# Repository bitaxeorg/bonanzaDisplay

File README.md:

# bonanzaDisplay v3.1

bonanzaDisplay is an open hardware OLED display and rotary-encoder controller
for **bitaxeBonanza-1004x**. An onboard Raspberry Pi RP2354A drives the display,
reads the encoder and its push button, and connects to the host ESP32 through
a single flat-flex cable carrying power, communication signals, and debug access.

This repository contains the **v3.1 KiCad hardware design**. Firmware, the
display UI, and the host communication protocol are not included here.

*Component-side render; the OLED panel faces the other side of the board.*

## Hardware overview

| Function | Implementation |
| --- | --- |
| Controller | Raspberry Pi RP2354A |
| Display | 3.12-inch, 256 × 64 OLED module using an SSD1322 controller |
| Display interface | 8-bit 8080 parallel bus |
| User input | Rotary encoder with push button (SW3) |
| Host connection | 12-pin, 1.0 mm pitch FFC connector (J5) |
| Host signals | TX/RX, two GPIO signals, SWDIO, and SWCLK |
| Power input | Nominal 12 V through J5 or the J2 bench-power pads |
| Logic supply | 3.3 V from a TPS62933 buck regulator |
| Development | USB-C (J6), SWD pads (J15), BOOT and RESET buttons |
| PCB | Six layers, with filled and copper-capped through vias |

The RP2354A handles the display and local controls, allowing the host to send
application data rather than drive the OLED bus directly. The actual UI and
division of work between the two processors depend on firmware.

## Connecting the board

### Host cable and J5 pinout

The intended connection is display J5 to **J5 on bitaxeBonanza-1004x**:

- Display connector: **JUSHUO AFA01-S12FCA-00**, LCSC C262757, bottom contact.
- Host connector: **TE 1-1735042-2**, LCSC C3169702.
- Cable: **12 conductors, 1.0 mm pitch, same-side exposed contacts**, with
  nominal 0.3 mm mating thickness. An example is SHOUHAN FFC-1.0-12P-50mm,
  **LCSC C6936374**.

For this connector pair, the standard same-side cable connects display pin
`n` to host pin `13 − n`. This numbering reversal is intentional; a custom
crossover cable is not required. Verify pin 1 and contact orientation before
applying power, since an incorrect connection can put 12 V on debug signals.

| Display J5 pin | Host J5 pin | Display net | RP2354A connection |
| --- | --- | --- | --- |
| 1 | 12 | 12V | Power input |
| 2 | 11 | 12V | Power input |
| 3 | 10 | GND | Ground |
| 4 | 9 | GND | Ground |
| 5 | 8 | DISP_GPIO1 | GPIO22 |
| 6 | 7 | DISP_GPIO2 | GPIO23 |
| 7 | 6 | GND | Ground |
| 8 | 5 | DISP_TX | GPIO21 |
| 9 | 4 | DISP_RX | GPIO20 |
| 10 | 3 | GND | Ground |
| 11 | 2 | SWD | SWDIO |
| 12 | 1 | SWCLK | SWCLK |

TX/RX above are the schematic net names. Firmware must implement the serial
interface on these exact GPIOs; the names do not establish a hardware UART
pin-mux configuration.

At the display's bottom-contact connector, the exposed cable contacts face
the PCB. At the TE host connector, they face the even-numbered solder-tail
side. Connector verification is recorded in
[issue #16](https://github.com/bitaxeorg/bonanzaDisplay/issues/16).

### OLED module and J1

J1 is a **JUSHUO AFC07-S30ECA-00** (LCSC C262645), a 30-contact, 0.5 mm pitch,
top-contact connector for nominal 0.3 mm flex. The OLED ribbon's physical
fit and contact orientation have been checked against the intended module.

The [EA W256064-XALG datasheet](https://www.lcd-module.de/fileadmin/html-seiten/eng/pdf/grafik/W256064-XALG.pdf)
is the reference for the module interface and electrical requirements.
Similar modules are sold under several manufacturer part numbers; check the
pinout, voltage requirements, and ribbon orientation of the exact module
being purchased rather than relying on screen size or controller name alone.

**Keep the project's custom J1 footprint.** Its pad numbers follow the OLED
module's numbering: KiCad pad `n` corresponds to connector drawing circuit
`31 − n`. Replacing it with a generic footprint without checking this mapping
can reverse the interface. Pads 31 and 32 are the grounded mounting tabs.

### Power

The host normally supplies 12 V through J5. For standalone development,
supply **J2 pin 1 with 12 V and J2 pin 2 with GND**. J2 is an optional header
location; the header is excluded from the current PCBA assembly selection.
**USB does not power the board.**

U4 converts 12 V to 3.3 V for the MCU and OLED logic. The OLED's VCI and
VDDIO inputs both use 3.3 V; separate 3.0 V and 2.8 V regulators are not
needed in this revision. The RP2354A's internal regulator supplies its core
through L1.

The OLED panel supply, VCC, connects directly to 12 V. There is no MCU-controlled
load switch or independent VCC sequencing. This is an accepted limitation of
v3.1, tracked in [issue #7](https://github.com/bitaxeorg/bonanzaDisplay/issues/7).
Firmware delays cannot switch this hardwired rail.

## Firmware interfaces

### Display

The hardware straps select **8-bit 8080 mode** (BS1 high, BS0 low).

| Function | RP2354A GPIO | J1 pin |
| --- | --- | --- |
| D0–D7 | GPIO0–GPIO7, respectively | 13 down to 6 |
| Reset, active low | GPIO8 | 20 |
| Chip select, active low | GPIO9 | 19 |
| Data/command | GPIO10 | 18 |
| Write strobe, active low | GPIO11 | 15 |
| Read strobe, active low | GPIO12 | 14 |

Use 8080 bus timing, and keep RD inactive for write-only operation. The
reference module's example SPI transport cannot be copied unchanged.

The OLED's VDD pin has a bypass capacitor but no external supply, so
initialization must enable the SSD1322's internal VDD regulator. Initialization
must also match the fitted external VSL diode/resistor network and the exact
module's reset and startup timing. See the reference module datasheet above.

### Encoder

| SW3 contact / net | RP2354A GPIO | Pull-up to 3.3 V |
| --- | --- | --- |
| B / SW_CW | GPIO13 | R41, 4.7 kΩ |
| S / SW_SW (push button) | GPIO14 | R42, 4.7 kΩ |
| A / SW_CCW | GPIO15 | R43, 4.7 kΩ |

The common contact is grounded. External 4.7 kΩ pull-ups provide approximately
0.70 mA through each closed contact, exceeding the selected HanElectricity
encoder's 0.5 mA minimum per phase. The MCU's internal pull-ups alone do not
meet that contact-current specification. R41–R43 use UNI-ROYAL
0402WGF4701TCE / LCSC C25900, a 0402, ±1% resistor listed as a JLCPCB Basic part
when selected. See the [encoder datasheet, page 2](https://datasheet.lcsc.com/datasheet/pdf/48f6c88fa6dacc08326345335965b3eb.pdf).

Configure the GPIOs as inputs with internal pull-downs disabled; external
resistors provide the pull-ups. Implement quadrature decoding and switch
debounce, and confirm rotation direction on the assembled board. The CW/CCW
net labels alone do not determine the decoder's sign.

## Programming and development

SW1 is **RESET** and SW2 is **BOOT**. The BOOT button connects to the QSPI
chip-select signal through R40, a 1 kΩ series resistor.

For SWD, use the host connector or the optional J15 header pads:

| J15 pin | Signal |
| --- | --- |
| 1 | SWCLK |
| 2 | GND |
| 3 | SWDIO |

Use a debugger compatible with 3.3 V logic and power the board externally.
J15 does not provide a target-voltage reference pin, and its header is excluded
from the current PCBA assembly selection.

The intended field-update path is the host ESP32 programming the RP2354A
through J5's SWD signals. ESP32 SWD support and the complete field-update
workflow still require firmware implementation and validation.

### Development-only USB port

J6 provides USB for development with external 12 V power. This revision
intentionally accepts the following limitations:

- **No VBUS sensing.** VBUS connects only to J6 and test point TP64. The MCU
  cannot detect when a host or hub removes VBUS, so its D+ attachment pull-up
  can remain enabled while the board stays powered. This does not meet the
  USB requirement to remove the attachment pull-up when VBUS is absent and
  can source current into an unpowered host's data input. Disconnect USB
  before shutting down the host/hub or disabling its port power while the
  board remains on. Normal suspend with VBUS present is a different condition.
- **No external USB ESD array.** The port relies on the MCU's internal
  protection and has not been validated for exposed production use or
  system-level ESD immunity. Use normal ESD precautions during development.

These choices are recorded in
[issue #14](https://github.com/bitaxeorg/bonanzaDisplay/issues/14); they are not
a claim of full USB compliance. Revisit them if USB becomes a user-facing port.

A future production variant could omit J6 and USB-only resistors R2, R4,
R37, and R38. **The current design still fits these parts**; no USB DNP
assembly variant has been implemented.

## Working with the design

Open [bonanzaDisplay.kicad_pro](bonanzaDisplay.kicad_pro) in **KiCad 10**.
Keep the repository's library tables, custom libraries, and 3D models together;
the library tables use project-relative paths.

| Path | Contents |
| --- | --- |
| [bonanzaDisplay.kicad_sch](bonanzaDisplay.kicad_sch) | Schematic |
| [bonanzaDisplay.kicad_pcb](bonanzaDisplay.kicad_pcb) | Six-layer PCB layout |
| [bonanzaDisplay.kicad_dru](bonanzaDisplay.kicad_dru) | Custom fabrication rules |
| [bonanzaDisplay.kicad_sym](bonanzaDisplay.kicad_sym) | Project symbol library |
| [bonanzaDisplay.pretty/](bonanzaDisplay.pretty/) | Project footprints |
| [3dshapes/](3dshapes/) | Component and module models |
| [fabrication-toolkit-options.json](fabrication-toolkit-options.json) | Saved Fabrication Toolkit export options |
| [docs/manufacturing.md](docs/manufacturing.md) | Fabrication, via filling, stencil, and assembly requirements |

After schematic changes, update the PCB, refill zones, and run ERC and DRC
including schematic/PCB parity before generating new manufacturing outputs.
Preserve the intentional connector numbering and review placement offsets
when replacing footprints or changing export tools.

## Manufacturing and project status

The board targets JLCPCB's standard **six-layer, 1 oz outer-copper process
with a routed outline**. It requires **epoxy-filled and copper-capped vias
(POFV)**, including vias in solder pads. Tenting alone is insufficient.
The design was reviewed against JLCPCB's no-extra-cost six-layer options on
2026-10-14; confirm the actual quote and process selections when ordering.

Read the [manufacturing guide](docs/manufacturing.md) before generating or
uploading Gerbers, a BOM, or a component placement file. The OLED module and
host FFC cable are separate assembly items, not parts installed by the board
assembly BOM.

At hardware commit [`0fab1ca`](https://github.com/bitaxeorg/bonanzaDisplay/commit/0fab1cac237adbfad9c7c31abaaa868e837f4df0),
KiCad 10.0.6 checks passed with no ERC findings, DRC violations, unconnected
items, or schematic/PCB parity findings. These checks do not establish
assembled-board operation or approve a production order. Remaining work includes:

- Resolving the effective-capacitance and inductor qualification findings in
  the [selected-part ratings review](docs/part-ratings.md).
- Checking final supplier part matches and placement corrections after the
  source BOM metadata reconciliation
  ([#13](https://github.com/bitaxeorg/bonanzaDisplay/issues/13)).
- Confirming filled/capped vias and the supplier's final stencil/CAM treatment
  ([#12](https://github.com/bitaxeorg/bonanzaDisplay/issues/12)).
- Reviewing the final assembly preview and validating firmware and assembled
  hardware, including display startup, encoder input, oscillator operation,
  BOOT, USB, and the intended host update workflow
  ([#17](https://github.com/bitaxeorg/bonanzaDisplay/issues/17)).

Use the [issue tracker](https://github.com/bitaxeorg/bonanzaDisplay/issues)
for review findings, accepted limitations, and their resolution. When reporting
a problem, include the board revision, hardware/firmware commits, exact OLED
module, and steps to reproduce it.

## License

The hardware design is licensed under the
**CERN Open Hardware Licence v2 — Strongly Reciprocal (CERN-OHL-S-2.0)**.
See [LICENSE](LICENSE) for the full terms.

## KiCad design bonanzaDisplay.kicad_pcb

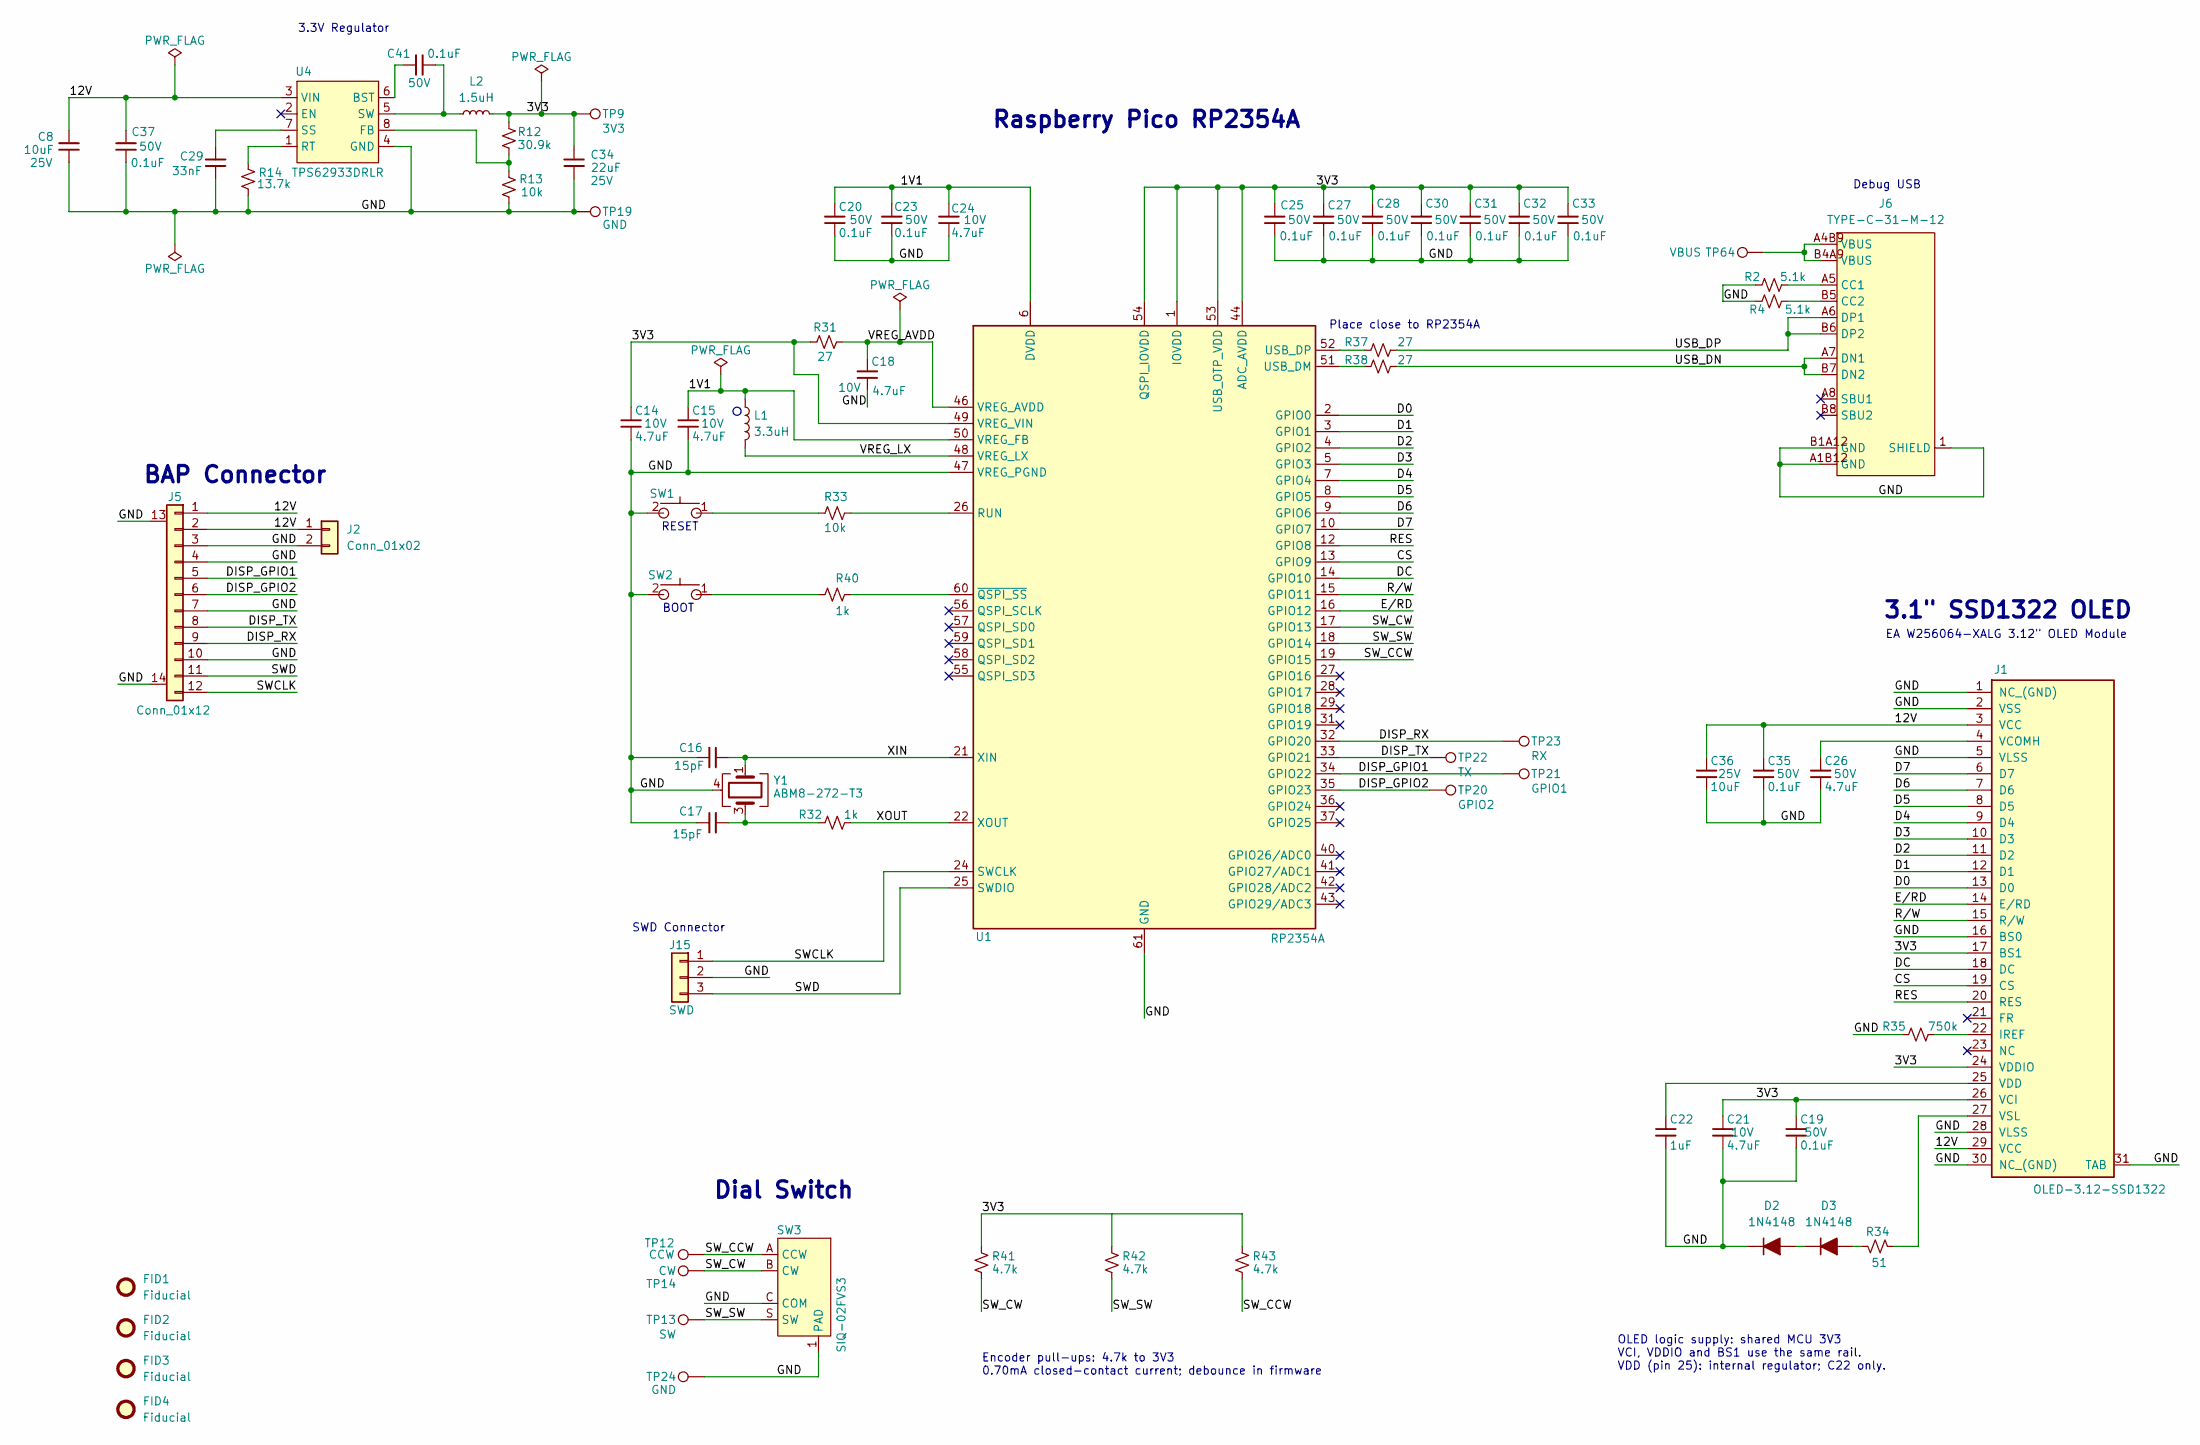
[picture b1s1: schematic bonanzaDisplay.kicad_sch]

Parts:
C8: 10uF; C_0805_2012Metric; Voltage 25V; Tolerance ±10%; PARTNO CL21A106KAYNNNE; LCSC C15850
C14: 4.7uF; C_0402_1005Metric; Voltage 10V; Previous voltage requir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 6.6V; PARTNO CL05A475MP5NRNC; LCSC C23733
C15, C18, C24: 4.7uF; C_0402_1005Metric; Voltage 10V; Previous voltage requir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 2.2V; PARTNO CL05A475MP5NRNC; LCSC C23733
C16, C17: 15pF; C_0402_1005Metric; Tolerance ±5%; Voltage 50V; PARTNO 0402CG150J500NT; LCSC C1548
C19: 0.1uF; C_0402_1005Metric; Voltage 50V; Previous voltage requir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 6V; PARTNO GRM155R71H104KE14D; LCSC C77020
C20, C23: 0.1uF; C_0402_1005Metric; Voltage 50V; Previous voltage requir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 2.2V; PARTNO GRM155R71H104KE14D; LCSC C77020
C21: 4.7uF; C_0402_1005Metric; Voltage 10V; Previous voltage requir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 6V; PARTNO CL05A475MP5NRNC; LCSC C23733
C22: 1uF; C_0402_1005Metric; Tolerance ±10%; Voltage 25V; PARTNO CL05A105KA5NQNC; LCSC C52923
C25, C27, C28, C30, C31, C32, C33: 0.1uF; C_0402_1005Metric; Voltage 50V; Previous voltage requir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 6.6V; PARTNO GRM155R71H104KE14D; LCSC C77020
C26: 4.7uF; C_1206_3216Metric; Tolerance ±10%; Voltage 50V; PARTNO CL31B475KBHNNNE; LCSC C51205
C29: 33nF; C_0402_1005Metric; Tolerance ±10%; Voltage 50V; PARTNO CC0402KRX7R9BB333; LCSC C106862
C34: 22uF; C_0805_2012Metric; Voltage 25V; Previous voltage requir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 10V; PARTNO CL21A226MAQNNNE; LCSC C45783
C35: 0.1uF; C_0402_1005Metric; Voltage 50V; Previous voltage requir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 24V; PARTNO GRM155R71H104KE14D; LCSC C77020
C36: 10uF; C_0805_2012Metric; Voltage 25V; Previous voltage requir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 24V; PARTNO CL21A106KAYNNNE; LCSC C15850
C37: 0.1uF; C_0402_1005Metric; Voltage 50V; Previous voltage requir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 25V; PARTNO GRM155R71H104KE14D; LCSC C77020
C41: 0.1uF; C_0402_1005Metric; Voltage 50V; Previous voltage requir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 10V; PARTNO GRM155R71H104KE14D; LCSC C77020
D2, D3: 1N4148; D_SOD-523; PARTNO 1N4148WT; LCSC C917006
FID1, FID2, FID3, FID4: Fiducial; Fiducial_1mm_Mask2mm
J1: OLED-3.12-SSD1322; FPC-SMD_P0.50-30P_LCS-SJ-H2.0; PARTNO AFC07-S30ECA-00; LCSC C262645
J2: Conn_01x02; PinHeader_1x02_P2.54mm_Vertical
J5: Conn_01x12; FPC-SMD_12P-P1.00_FGS-XJ-H2.0; PARTNO AFA01-S12FCA-00; LCSC C262757
J6: TYPE-C-31-M-12; USB-C_SMD-TYPE-C-31-M-12_1; PARTNO TYPE-C-31-M-12; LCSC C165948
J15: SWD; PinHeader_1x03_P2.54mm_Vertical
L1: 3.3uH; IND-SMD-L2.0-W1.6-MLP2016H3R3MT0S1; PARTNO MLP2016H3R3MT0S1; LCSC C383379
L2: 1.5uH; IND-SMD_L2.0-W1.6; PARTNO FTC201612S1R5MBCA; LCSC C5832350
R2, R4: 5.1k; R_0402_1005Metric; Tolerance ±1%; Voltage 50V; PARTNO 0402WGF5101TCE; LCSC C25905
R12: 30.9k; R_0402_1005Metric; Tolerance ±1%; Voltage 50V; PARTNO 0402WGF3092TCE; LCSC C270615
R13, R33: 10k; R_0402_1005Metric; Tolerance ±1%; Voltage 50V; PARTNO 0402WGF1002TCE; LCSC C25744
R14: 13.7k; R_0402_1005Metric; Tolerance ±1%; Voltage 50V; PARTNO RC0402FR-0713K7L; LCSC C274888
R31, R37, R38: 27; R_0402_1005Metric; Tolerance ±1%; Voltage 50V; PARTNO RC0402FR-0727RL; LCSC C138021
R32: 1k; R_0402_1005Metric; Tolerance ±1%; Voltage 50V; PARTNO 0402WGF1001TCE; LCSC C11702
R34: 51; R_0402_1005Metric; Tolerance ±1%; Voltage 50V; PARTNO RC0402FR-0751RL; LCSC C137960
R35: 750k; R_0402_1005Metric; Tolerance ±1%; Voltage 50V; PARTNO 0402WGF7503TCE; LCSC C122545
R40: 1k; R_0402_1005Metric; Tolerance ±1%; Voltage 50V; MPN 0402WGF1001TCE; LCSC C11702
R41, R42, R43: 4.7k; R_0402_1005Metric; Tolerance ±1%; Voltage 50V; PARTNO 0402WGF4701TCE; LCSC C25900
SW1, SW2: TS-1088-AR02016; SW-SMD_L3.9-W3.0-P4.45; PARTNO TS-1088-AR02016; LCSC C720477
SW3: SIQ-02FVS3; SW-SMD_SIQ-02FVS3; PARTNO SIQ-02FVS3; LCSC C41430892
TP9: 3V3; TestPoint_Pad_D1.0mm
TP12: CCW; TestPoint_Pad_D1.0mm
TP13: SW; TestPoint_Pad_D1.0mm
TP14: CW; TestPoint_Pad_D1.0mm; LCSC C344022
TP19, TP24: GND; TestPoint_Pad_D1.0mm; LCSC C138021
TP20: GPIO2; TestPoint_Pad_D1.0mm
TP21: GPIO1; TestPoint_Pad_D1.0mm
TP22: TX; TestPoint_Pad_D1.0mm
TP23: RX; TestPoint_Pad_D1.0mm
TP64: VBUS; TestPoint_Pad_D1.0mm
U1: RP2354A; QFN-60-1EP_7x7mm_P0.4mm_EP3.4x3.4mm; PARTNO RP2354A; LCSC C41378174
U4: TPS62933DRLR; SOT-583-8_L2.1-W1.2-P0.50-LS1.6-BR; PARTNO TPS62933DRLR; LCSC C3200405
Y1: ABM8-272-T3; Crystal_SMD_3225-4Pin_3.2x2.5mm; PARTNO ABM8-272-T3; LCSC C20625731

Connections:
/1V1: C15.1, C20.1, C23.1, C24.1, L1.1, U1.6 (DVDD), U1.23 (DVDD), U1.39 (DVDD), U1.50 (VREG_FB)
/3V3: C14.1, C19.1, C21.1, C25.1, C27.1, C28.1, C30.1, C31.1, C32.1, C33.1, C34.2, J1.17 (BS1), J1.24 (VDDIO), J1.26 (VCI), L2.2, R12.2, R31.2, R41.1, R42.1, R43.1, TP9.1 (1_1), U1.1 (IOVDD), U1.11 (IOVDD), U1.20 (IOVDD), U1.30 (IOVDD), U1.38 (IOVDD), U1.44 (ADC_AVDD), U1.45 (IOVDD), U1.49 (VREG_VIN), U1.53 (USB_OTP_VDD), U1.54 (QSPI_IOVDD)
/12V: C8.2, C35.1, C36.1, C37.1, J1.3 (VCC), J1.29 (VCC), J2.1, J5.1, J5.2, U4.3 (VIN)
/CS: J1.19 (CS), U1.13 (GPIO9)
/D0: J1.13 (D0), U1.2 (GPIO0)
/D1: J1.12 (D1), U1.3 (GPIO1)
/D2: J1.11 (D2), U1.4 (GPIO2)
/D3: J1.10 (D3), U1.5 (GPIO3)
/D4: J1.9 (D4), U1.7 (GPIO4)
/D5: J1.8 (D5), U1.8 (GPIO5)
/D6: J1.7 (D6), U1.9 (GPIO6)
/D7: J1.6 (D7), U1.10 (GPIO7)
/DC: J1.18 (DC), U1.14 (GPIO10)
/DISP_GPIO1: J5.5, TP21.1 (1_1), U1.34 (GPIO22)
/DISP_GPIO2: J5.6, TP20.1 (1_1), U1.35 (GPIO23)
/DISP_RX: J5.9, TP23.1 (1_1), U1.32 (GPIO20)
/DISP_TX: J5.8, TP22.1 (1_1), U1.33 (GPIO21)
/E/RD: J1.14 (E/RD), U1.16 (GPIO12)
/GND: C8.1, C14.2, C15.2, C16.2, C17.2, C18.2, C19.2, C20.2, C21.2, C22.2, C23.2, C24.2, C25.2, C26.2, C27.2, C28.2, C29.1, C30.2, C31.2, C32.2, C33.2, C34.1, C35.2, C36.2, C37.2, D2.1 (K), J1.1 (NC_(GND)), J1.2 (VSS), J1.5 (VLSS), J1.16 (BS0), J1.28 (VLSS), J1.30 (NC_(GND)), J1.31 (TAB), J1.32 (TAB), J2.2, J5.3, J5.4, J5.7, J5.10, J5.13, J5.14, J6.1 (SHIELD), J6.2 (EH), J6.3 (EH), J6.4 (EH), J6.A1B12 (GND), J6.B1A12 (GND), J15.2, R2.1, R4.1, R13.1, R14.1, R35.2, SW1.2, SW2.2, SW3.1 (PAD), SW3.2 (PAD), SW3.C (COM), TP19.1 (1_1), TP24.1 (1_1), U1.47 (VREG_PGND), U1.61 (GND), U4.4 (GND), Y1.2, Y1.4
/RES: J1.20 (RES), U1.12 (GPIO8)
/R/W: J1.15 (R/W), U1.15 (GPIO11)
/SWCLK: J5.12 (Pin_10), J15.1, U1.24 (SWCLK)
/SWD: J5.11 (Pin_10), J15.3, U1.25 (SWDIO)
/SW_CCW: R43.2, SW3.A (CCW), TP12.1 (1_1), U1.19 (GPIO15)
/SW_CW: R41.2, SW3.B (CW), TP14.1 (1_1), U1.17 (GPIO13)
/SW_SW: R42.2, SW3.S (SW), TP13.1 (1_1), U1.18 (GPIO14)
/USB_DN: J6.A7 (DN1), J6.B7 (DN2), R38.1
/USB_DP: J6.A6 (DP1), J6.B6 (DP2), R37.1
/VREG_AVDD: C18.1, R31.1, U1.46 (VREG_AVDD)
/VREG_LX: L1.2, U1.48 (VREG_LX)
/XIN: C16.1, U1.21 (XIN), Y1.1
/XOUT: R32.1, U1.22 (XOUT)
unnamed: C17.1, R32.2, Y1.3
unnamed: D2.2 (A), D3.1 (K)
unnamed: D3.2 (A), R34.1
unnamed: J1.22 (IREF), R35.1
unnamed: C26.1, J1.4 (VCOMH)
unnamed: C22.1, J1.25 (VDD)
unnamed: J1.27 (VSL), R34.2
unnamed: J6.A5 (CC1), R2.2
unnamed: J6.B5 (CC2), R4.2
unnamed: J6.A4B9 (VBUS), J6.B4A9 (VBUS), TP64.1 (1_1)
unnamed: R33.2, SW1.1
unnamed: R40.2, SW2.1
unnamed: R33.1, U1.26 (RUN)
unnamed: R38.2, U1.51 (USB_DM)
unnamed: R37.2, U1.52 (USB_DP)
unnamed: R40.1, U1.60 (~QSPI_SS)
unnamed: C41.1, U4.6 (BST)
unnamed: R12.1, R13.2, U4.8 (FB)
unnamed: R14.2, U4.1 (RT)
unnamed: C29.2, U4.7 (SS)
unnamed: C41.2, L2.1, U4.5 (SW)

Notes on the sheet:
Place close to RP2354A
Encoder pull-ups: 4.7k to 3V3 0.70mA closed-contact current; debounce in firmware
EA W256064-XALG 3.12" OLED Module
Debug USB
BOOT
SWD Connector
Raspberry Pico RP2354A
3.3V Regulator
OLED logic supply: shared MCU 3V3 VCI, VDDIO and BS1 use the same rail. VDD (pin 25): internal regulator; C22 only.
Dial Switch
3.1" SSD1322 OLED
BAP Connector
RESET

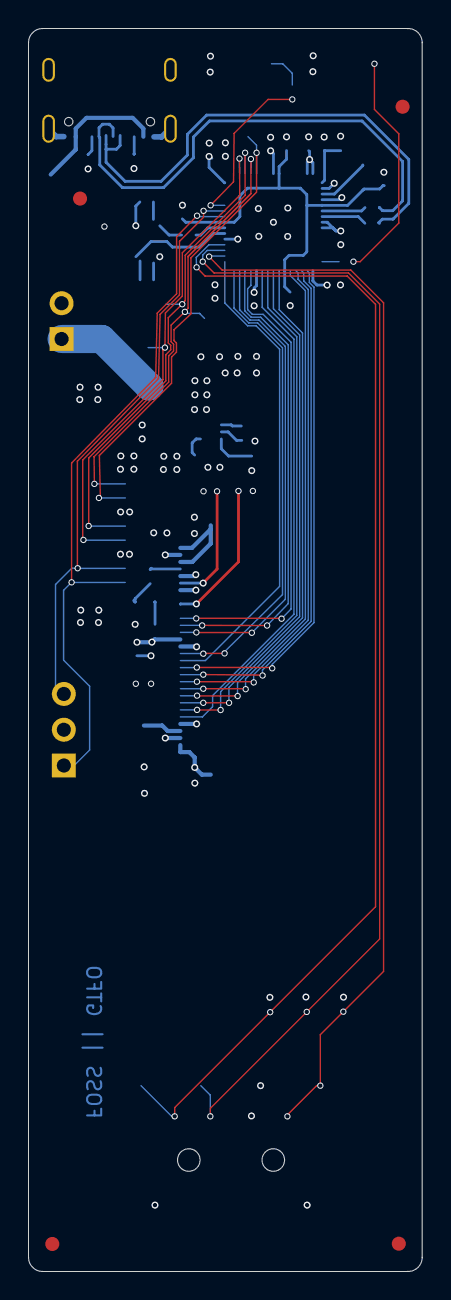
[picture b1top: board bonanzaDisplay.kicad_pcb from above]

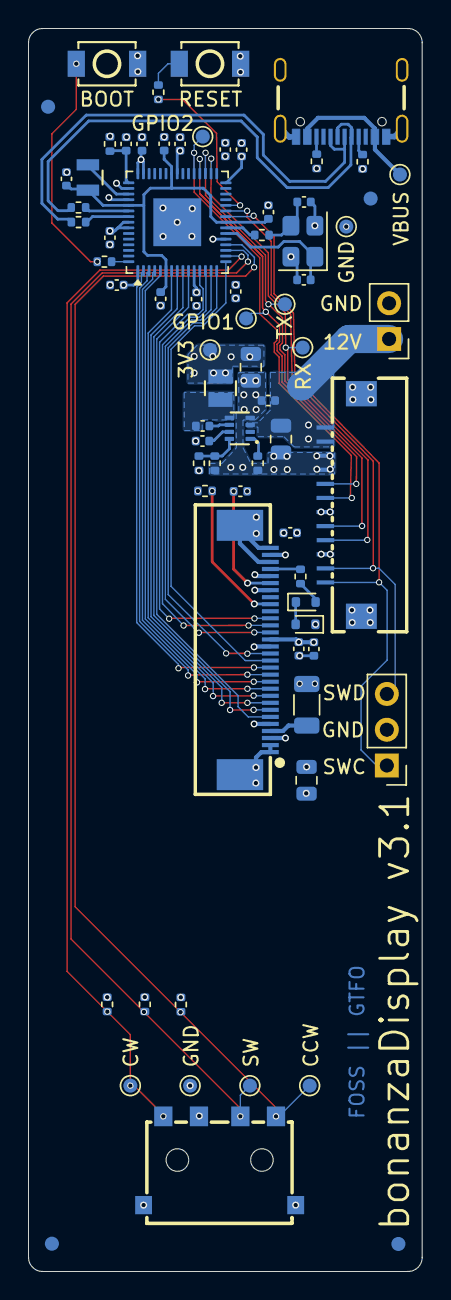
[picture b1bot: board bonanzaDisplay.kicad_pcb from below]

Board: 6 copper layers, 27.9 x 88.2 mm, 72 parts (68 on the bottom side), 53 nets.

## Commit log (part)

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2026-04-09 initial import
2026-04-09 add display connector and circuit
2026-04-10 updated display circuit with reference design
2026-04-10 added nav switch. added part footprints to local library
2026-04-10 added more local footprints. brought over edge cuts from bitaxeBonanza. Placed display
2026-04-11 added missing 3d CAD. finished routing
2026-04-11 routing cleanup
2026-04-13 updated RP2354A inductor footprint. fixed USB port position. fixed corrupted footprint library
2026-04-13 updated LCSC part numbers
2026-04-13 switched to dial switch. added OLED 3D CAD. ordered PCBA
2026-05-05 add OHLv2 license
2026-05-06 fix display connector pinout for #1
2026-05-06 switched 10pin FFC connector to right angle. made PCB shorter. most routing done.
2026-05-06 cleanup footprints
2026-05-06 DRC pass, updated BOM
2026-05-07 added manual 12V header
2026-05-07 test point arrangement
2026-05-07 DRC/Library cleanup
2026-05-08 updated BOM with some cheaper JLC Basic parts
